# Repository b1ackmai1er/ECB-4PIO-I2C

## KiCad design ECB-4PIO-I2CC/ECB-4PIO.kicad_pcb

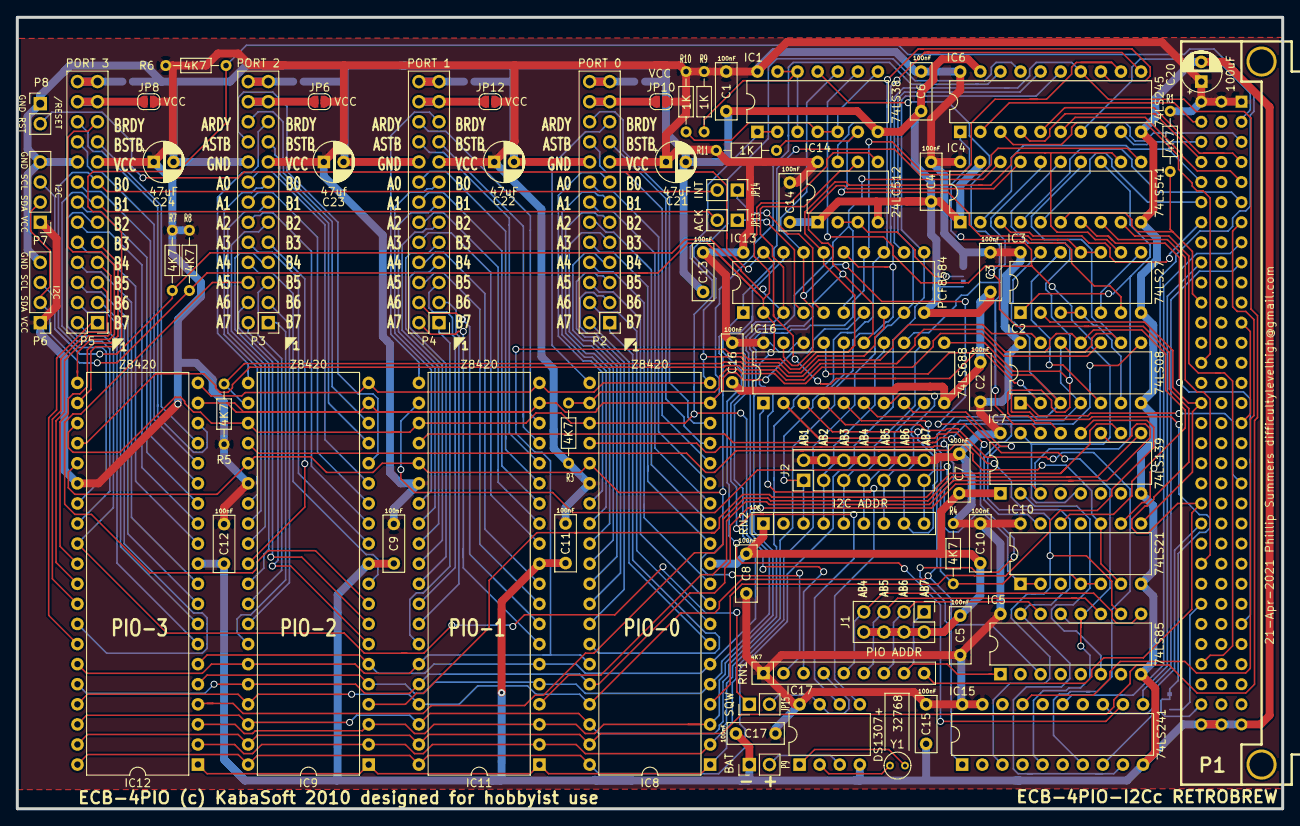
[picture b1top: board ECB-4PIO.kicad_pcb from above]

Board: 2 copper layers, 160.0 x 100.1 mm, 76 parts (0 on the bottom side), 181 nets.

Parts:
C1, C2, C3, C4, C5, C6, C7, C8, C9, C10, C11, C12, C13, C14, C15, C16, C17: 100nF; C_Disc_D7.0mm_W2.5mm_P5.00mm
C20: 100uF; CP_Radial_D5.0mm_P2.50mm
C21, C22, C24: 47uF; CP_Radial_D5.0mm_P2.50mm
C23: 47uf; CP_Radial_D5.0mm_P2.50mm
IC1: 74LS38; DIP-14_W7.62mm
IC2: 74LS08; DIP-14_W7.62mm
IC3: 74LS27; DIP-14_W7.62mm
IC4: 74LS541; DIP-20_W7.62mm
IC5: 74LS85; DIP-16_W7.62mm
IC6: 74LS245; DIP-20_W7.62mm
IC7: 74LS139; DIP-16_W7.62mm
IC8, IC9, IC11, IC12: Z8420; DIP-40_W15.24mm
IC10: 74LS21; DIP-14_W7.62mm
IC13: PCF8584; DIP-20_W7.62mm
IC14: 24LC512; DIP-8_W7.62mm
IC15: 74LS241; DIP-20_W7.62mm
IC16: 74LS688; DIP-20_W7.62mm
IC17: DS1307+; DIP-8_W7.62mm
J1: PIO ADDR; PinHeader_2x04_P2.54mm_Vertical
J2: I2C ADDR; PinHeader_2x07_P2.54mm_Vertical
JP1: ADRSEL; SolderJumper-3_P1.3mm_Bridged12_RoundedPad1.0x1.5mm_NumberL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
JP2: RESSEL; SolderJumper-3_P1.3mm_Bridged12_RoundedPad1.0x1.5mm_NumberL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
JP5, JP7, JP9, JP11: GND; SolderJumper-2_P1.3mm_Open_RoundedPad1.0x1.5mm
JP6, JP8, JP10, JP12: VCC; SolderJumper-2_P1.3mm_Open_RoundedPad1.0x1.5mm
JP13: ACK; PinHeader_1x02_P2.54mm_Vertical
JP14: INT; PinHeader_1x02_P2.54mm_Vertical
JP15: SQW; PinHeader_1x02_P2.54mm_Vertical
P1: C96ABC; C96ABCMC
P2: PORT 0; PinHeader_2x13_P2.54mm_Vertical
P3: PORT 2; PinHeader_2x13_P2.54mm_Vertical
P4: PORT 1; PinHeader_2x13_P2.54mm_Vertical
P5: PORT 3; PinHeader_2x13_P2.54mm_Vertical
P6, P7: I2C; PinHeader_1x04_P2.54mm_Vertical
P8: /RESET; PinHeader_1x02_P2.54mm_Vertical
P9: BAT; PinHeader_1x02_P2.54mm_Vertical
R1, R3, R4, R5, R6, R7, R8: 4K7; R_Axial_DIN0204_L3.6mm_D1.6mm_P7.62mm_Horizontal
R9, R10, R11: 1K; R_Axial_DIN0204_L3.6mm_D1.6mm_P7.62mm_Horizontal
RN1: 4K7; R_Array_SIP9
RN2: 10K; R_Array_SIP9
Y1: 32768; Crystal_Round_D3.0mm_Vertical

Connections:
/0A0: IC8.15, P2.16
/0A1: IC8.14, P2.14
/0A2: IC8.13, P2.12
/0A3: IC8.12, P2.10
/0A4: IC8.10, P2.8
/0A5: IC8.9, P2.6
/0A6: IC8.8, P2.4
/0A7: IC8.7, P2.2
/0ARDY: IC8.18, P2.22
/0ASTB: IC8.16, P2.20
/0B0: IC8.27, P2.15
/0B1: IC8.28, P2.13
/0B2: IC8.29, P2.11
/0B3: IC8.30, P2.9
/0B4: IC8.31, P2.7
/0B5: IC8.32, P2.5
/0B6: IC8.33, P2.3
/0B7: IC8.34, P2.1
/0BRDY: IC8.21, P2.21
/0BSTB: IC8.17, P2.19
/1A0: IC11.15, P4.16
/1A1: IC11.14, P4.14
/1A2: IC11.13, P4.12
/1A3: IC11.12, P4.10
/1A4: IC11.10, P4.8
/1A5: IC11.9, P4.6
/1A6: IC11.8, P4.4
/1A7: IC11.7, P4.2
/1ARDY: IC11.18, P4.22
/1ASTB: IC11.16, P4.20
/1B0: IC11.27, P4.15
/1B1: IC11.28, P4.13
/1B2: IC11.29, P4.11
/1B3: IC11.30, P4.9
/1B4: IC11.31, P4.7
/1B5: IC11.32, P4.5
/1B6: IC11.33, P4.3
/1B7: IC11.34, P4.1
/1BRDY: IC11.21, P4.21
/1BSTB: IC11.17, P4.19
/2A0: IC9.15, P3.16
/2A1: IC9.14, P3.14
/2A2: IC9.13, P3.12
/2A3: IC9.12, P3.10
/2A4: IC9.10, P3.8
/2A5: IC9.9, P3.6
/2A6: IC9.8, P3.4
/2A7: IC9.7, P3.2
/2ARDY: IC9.18, P3.22
/2ASTB: IC9.16, P3.20
/2B0: IC9.27, P3.15
/2B1: IC9.28, P3.13
/2B2: IC9.29, P3.11
/2B3: IC9.30, P3.9
/2B4: IC9.31, P3.7
/2B5: IC9.32, P3.5
/2B6: IC9.33, P3.3
/2B7: IC9.34, P3.1
/2BRDY: IC9.21, P3.21
/2BSTB: IC9.17, P3.19
/3A0: IC12.15, P5.16
/3A1: IC12.14, P5.14
/3A2: IC12.13, P5.12
/3A3: IC12.12, P5.10
/3A4: IC12.10, P5.8
/3A5: IC12.9, P5.6
/3A6: IC12.8, P5.4
/3A7: IC12.7, P5.2
/3ARDY: IC12.18, P5.22
/3ASTB: IC12.16, P5.20
/3B0: IC12.27, JP14.2, P5.15
/3B1: IC12.28, JP13.2, P5.13
/3B2: IC12.29, JP15.1, P5.11
/3B3: IC12.30, P5.9
/3B4: IC12.31, P5.7
/3B5: IC12.32, P5.5
/3B6: IC12.33, P5.3
/3B7: IC12.34, P5.1
/3BRDY: IC12.21, P5.21
/3BSTB: IC12.17, P5.19
//I/O-DECODE: IC1.9, IC7.5, IC7.15
//IORQ: IC3.1, IC4.13, IC7.3, IC8.36, IC9.36, IC11.36, IC12.36, IC16.1
/AB0: IC4.18, IC8.6, IC9.6, IC11.6, IC12.6, IC13.6
/AB1: IC4.17, IC8.5, IC9.5, IC11.5, IC12.5, IC16.15
/AB2: IC4.16, IC7.14, IC16.13
/AB3: IC4.15, IC7.13, IC16.11
/AB4: IC5.10, IC15.3, IC16.8
/AB5: IC5.12, IC15.5, IC16.6
/AB6: IC5.13, IC15.7, IC16.4
/AB7: IC5.15, IC15.9, IC16.2
/B_/BAI: P1.A12, P1.A17
/B_/INT: IC1.11, P1.C21, RN1.9
/B_/IORQ: IC4.7, P1.A27
/B_/M1: IC2.1, P1.A20
/B_/PWCLR: JP2.3, P1.C26
/B_/RESET: IC2.2, IC13.19, JP2.1, JP2.2, P1.C31, P8.2
/B_AB0: IC4.2, P1.C5
/B_AB1: IC4.3, P1.C7
/B_AB2: IC4.4, P1.A6
/B_AB3: IC4.5, P1.C6
/B_AB4: IC15.17, P1.A7
/B_AB5: IC15.15, P1.A8
/B_AB6: IC15.13, P1.A9
/B_AB7: IC15.11, P1.C9
/B_DB0: IC6.2, P1.C2
/B_DB1: IC6.3, P1.C14
/B_DB2: IC6.4, P1.C4
/B_DB3: IC6.5, P1.A4
/B_DB4: IC6.6, P1.A5
/B_DB5: IC6.7, P1.A2
/B_DB6: IC6.8, P1.A3
/B_DB7: IC6.9, P1.C3
/B_IEI: IC4.6, P1.C11, R1.2
/B_IEO: IC3.2, IC10.8, P1.C16
/B_PHI: IC4.9, P1.C29
/B_~RD: IC4.8, P1.C24
/B_~WR: IC15.8, P1.C22
/DB0: IC6.18, IC8.19, IC9.19, IC11.19, IC12.19, IC13.7
/DB1: IC6.17, IC8.20, IC9.20, IC11.20, IC12.20, IC13.8
/DB2: IC6.16, IC8.1, IC9.1, IC11.1, IC12.1, IC13.9
/DB3: IC6.15, IC8.40, IC9.40, IC11.40, IC12.40, IC13.11
/DB4: IC6.14, IC8.39, IC9.39, IC11.39, IC12.39, IC13.12
/DB5: IC6.13, IC8.38, IC9.38, IC11.38, IC12.38, IC13.13
/DB6: IC6.12, IC8.3, IC9.3, IC11.3, IC12.3, IC13.14
/DB7: IC6.11, IC8.2, IC9.2, IC11.2, IC12.2, IC13.15
/IEI: IC2.4, IC2.9, IC2.12, IC4.14, IC8.24, IC10.1, IC10.2
/IEO_0: IC2.8, IC10.13, IC11.24
/IEO_1: IC9.24, IC10.6, IC10.10
/IEO_2: IC2.11, IC10.12, IC12.24
/PHI: IC4.11, IC8.25, IC9.25, IC11.25, IC12.25, IC13.1, RN1.2
/PU3: IC1.4, IC1.5, IC1.8, R10.2
/SCL: IC13.3, IC14.6, IC17.6, P6.3, P7.3, R7.2
/SDA: IC13.2, IC14.5, IC17.5, P6.2, P7.2, R8.2
/SMA1: IC14.2, IC14.3, JP1.2
/SQW: IC17.7, JP15.2, RN1.4
/~CE-PCF: IC1.10, IC13.17, IC15.1, IC16.19
/~CE-PIO0: IC7.12, IC8.4
/~CE-PIO1: IC7.11, IC11.4
/~CE-PIO2: IC7.10, IC9.4
/~CE-PIO3: IC7.9, IC12.4
/~INT: IC1.1, IC1.2, IC8.23, IC9.23, IC11.23, IC12.23, RN1.3
/~M1-PIO: IC2.3, IC3.13, IC5.3, IC8.37, IC9.37, IC11.37, IC12.37, IC16.17
/~RD: IC3.9, IC4.12, IC8.35, IC9.35, IC11.35, IC12.35, IC13.16
/~WR: IC13.18, IC15.12
GND: C1.2, C2.2, C3.2, C4.2, C5.2, C6.2, C7.2, C8.2, C9.2, C10.2, C11.2, C12.2, C13.2, C14.2, C15.2, C16.2, C17.2, C20.2, C21.2, C22.2, C23.2, C24.2, IC1.7, IC2.7, IC3.7, IC4.1, IC4.10, IC4.19, IC5.8, IC6.10, IC6.19, IC7.1, IC7.8, IC8.11, IC9.11, IC10.7, IC11.11, IC12.11, IC13.10, IC14.1, IC14.4, IC14.7, IC15.10, IC16.10, IC17.4, J1.2, J1.4, J1.6, J1.8, JP1.1, JP5.1, JP7.1, JP9.1, JP11.1, P1.A32, P1.B32, P1.C32, P2.18, P3.18, P4.18, P5.18, P6.4, P7.4, P8.1, P9.1, RN2.1
unnamed: IC1.6, IC3.10, IC3.11, R11.2
unnamed: IC1.3, IC1.12, IC1.13, R9.2
unnamed: IC2.5, IC3.12
unnamed: IC2.6, IC3.3, IC3.4
unnamed: IC2.10, IC8.22, R3.2
unnamed: IC2.13, IC9.22, R5.2
unnamed: IC3.5, IC3.8
unnamed: IC3.6, IC6.1
unnamed: IC5.1, J1.1, RN1.8
unnamed: IC5.6, IC7.2
unnamed: IC5.9, J1.7, RN1.5
unnamed: IC5.11, J1.5, RN1.6
unnamed: IC5.14, J1.3, RN1.7
unnamed: IC10.4, IC10.5, IC11.22, R4.2
unnamed: IC10.9, IC12.22, R6.2
unnamed: IC13.4, JP13.1
unnamed: IC13.5, JP14.1
unnamed: IC16.3, J2.13, RN2.9
unnamed: IC16.5, J2.11, RN2.8
unnamed: IC16.7, J2.9, RN2.7
unnamed: IC16.9, J2.7, RN2.6
unnamed: IC16.12, J2.5, RN2.5
unnamed: IC16.14, J2.3, RN2.4
unnamed: IC16.16, J2.1, RN2.3
unnamed: IC17.1, Y1.2
unnamed: IC17.2, Y1.1
unnamed: IC17.3, P9.2
unnamed: JP5.2, P3.25, P3.26
unnamed: JP6.1, P3.23, P3.24
unnamed: JP7.2, P5.25, P5.26
unnamed: JP8.1, P5.23, P5.24
unnamed: JP9.2, P2.25, P2.26
unnamed: JP10.1, P2.23, P2.24
unnamed: JP11.2, P4.25, P4.26
unnamed: JP12.1, P4.23, P4.24
VCC: C1.1, C2.1, C3.1, C4.1, C5.1, C6.1, C7.1, C8.1, C9.1, C10.1, C11.1, C12.1, C13.1, C14.1, C15.1, C16.1, C17.1, C20.1, C21.1, C22.1, C23.1, C24.1, IC1.14, IC2.14, IC3.14, IC4.20, IC5.16, IC6.20, IC7.16, IC8.26, IC9.26, IC10.14, IC11.26, IC12.26, IC13.20, IC14.8, IC15.19, IC15.20, IC16.18, IC16.20, IC17.8, J2.2, J2.4, J2.6, J2.8, J2.10, J2.12, J2.14, JP1.3, JP6.2, JP8.2, JP10.2, JP12.2, P1.A1, P1.B1, P1.C1, P2.17, P3.17, P4.17, P5.17, P6.1, P7.1, R1.1, R3.1, R4.1, R5.1, R6.1, R7.1, R8.1, R9.1, R10.1, R11.1, RN1.1

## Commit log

2021-02-28 Version A - Initial release
2021-02-28 Version B - Add DS1307 RTC
2021-04-21 Version C- First working prototype
